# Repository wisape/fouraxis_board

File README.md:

# fouraxis_board-
A 4 axis board sch and pcb, which use the software KICAD

the board use the stm32
then sensor use mpu6050, and hmc5883l
and the wireless use nrf24l01

### pcb

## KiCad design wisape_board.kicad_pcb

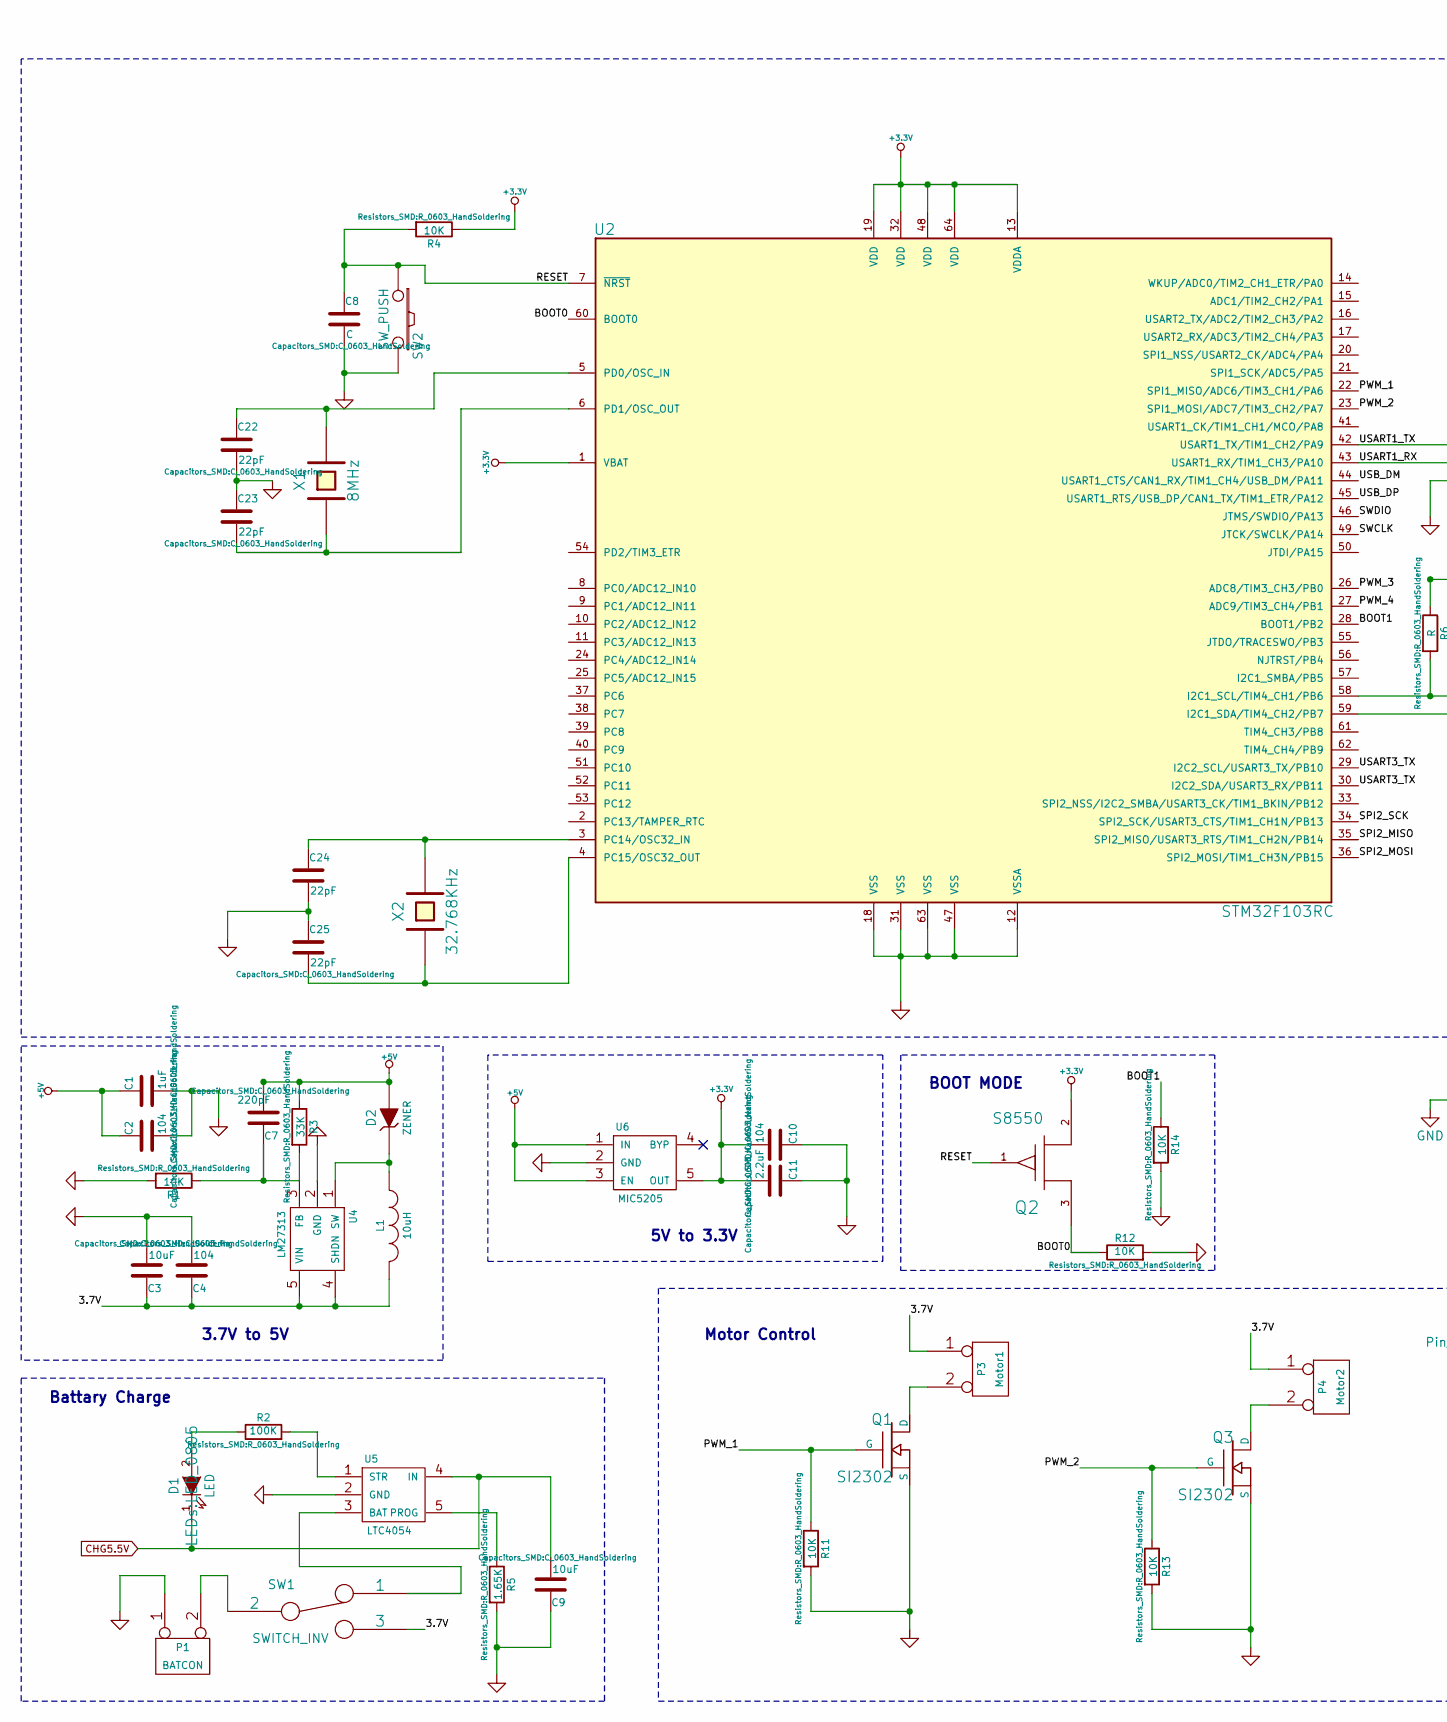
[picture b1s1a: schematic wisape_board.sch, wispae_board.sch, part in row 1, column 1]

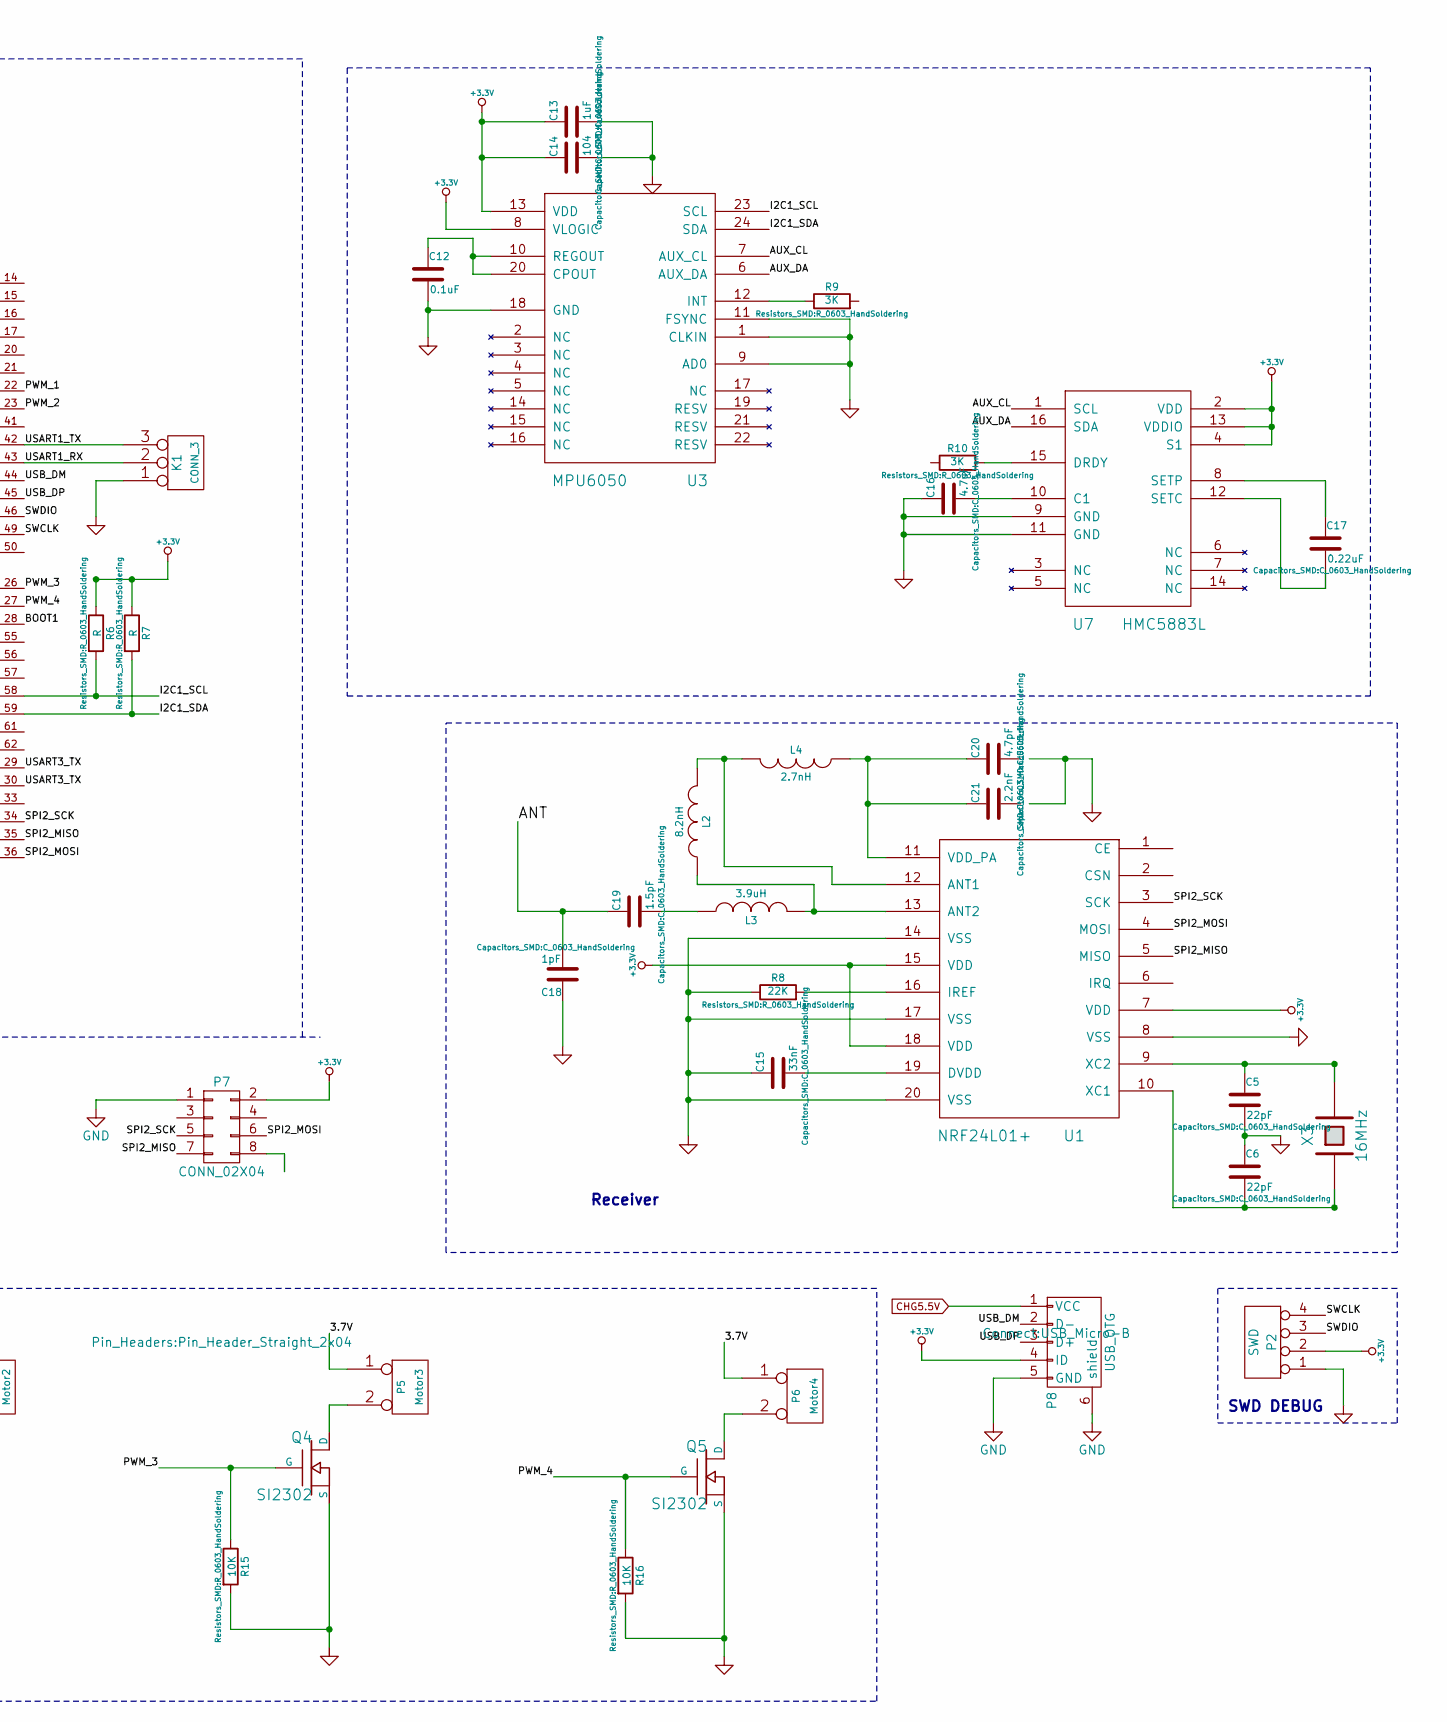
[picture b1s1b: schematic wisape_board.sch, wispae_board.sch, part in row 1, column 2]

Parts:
C1, C13: 1uF; C_0603_HandSoldering
C2, C4, C10, C14: 104; C_0603_HandSoldering
C3, C9: 10uF; C_0603_HandSoldering
C5, C6, C22, C23, C24, C25: 22pF; C_0603_HandSoldering
C7: 220pF; C_0603_HandSoldering
C8: C; C_0603_HandSoldering
C11: 2.2uF; C_0603_HandSoldering
C12: 0.1uF; C_0603_HandSoldering
C15: 33nF; C_0603_HandSoldering
C16: 4.7uF; C_0603_HandSoldering
C17: 0.22uF; C_0603_HandSoldering
C18: 1pF; C_0603_HandSoldering
C19: 1.5pF; C_0603_HandSoldering
C20: 4.7pF; C_0603_HandSoldering
C21: 2.2nF; C_0603_HandSoldering
D1: LED; LED_0805
D2: ZENER; SOD-123
K1: CONN_3; Pin_Header_Straight_1x03
L1: 10uH; Neosid_Inductor_SM0603CG
L2: 8.2nH; Neosid_Inductor_SM0603CG
L3: 3.9uH; Neosid_Inductor_SM0603CG
L4: 2.7nH; Neosid_Inductor_SM0603CG
P1: BATCON; Pin_Header_Straight_1x02
P2: SWD; Pin_Header_Straight_1x04
P3: Motor1; Pin_Header_Straight_1x02
P4: Motor2; Pin_Header_Straight_1x02
P5: Motor3; Pin_Header_Straight_1x02
P6: Motor4; Pin_Header_Straight_1x02
P7: CONN_02X04; Pin_Header_Straight_2x04
P8: USB_OTG; USB_Micro-B
Q1, Q3, Q4, Q5: SI2302; SOT-23
Q2: S8550; SOT-23
R1, R4, R11, R12, R13, R14, R15, R16: 10K; R_0603_HandSoldering
R2: 100K; R_0603_HandSoldering
R3: 33K; R_0603_HandSoldering
R5: 1.65K; R_0603_HandSoldering
R6, R7: R; R_0603_HandSoldering
R8: 22K; R_0603_HandSoldering
R9, R10: 3K; R_0603_HandSoldering
SW1: SWITCH_INV; SW_Micro_SPST
SW2: SW_PUSH; Switch_SMD_3_6_2.5
U1: NRF24L01+; QFN-20-1EP_4x4mm_Pitch0.5mm
U2: STM32F103RC; LQFP-64_10x10mm_Pitch0.5mm
U3: MPU6050; QFN-24-1EP_4x4mm_Pitch0.5mm
U4: LM27313; SOT-23-5
U5: LTC4054; SOT-23-5
U6: MIC5205; SOT-23-5
U7: HMC5883L; QFN-16-1EP_3x3mm_Pitch0.5mm
X1: 8MHz; Crystal_HC49-SD_SMD
X2: 32.768KHz; Crystal_Round_Vertical_3mm
X3: 16MHz; Crystal_HC49-SD_SMD

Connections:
+3.3V: C10.2, C11.2, C13.1, C14.1, P2.2, P7.2, P8.4 (ID), Q2.2 (S), R4.1, R6.1, R7.1, U1.7 (VDD), U1.15 (VDD), U1.18 (VDD), U2.1 (VBAT), U2.13 (VDDA), U2.19 (VDD), U2.32 (VDD), U2.48 (VDD), U2.64 (VDD), U3.8 (VLOGIC), U3.13 (VDD), U6.5 (OUT), U7.2 (VDD), U7.4 (S1), U7.13 (VDDIO)
+5V: C1.1, C2.1, C7.2, D2.2 (A), R3.1, U6.1 (IN), U6.3 (EN)
/3.7V: C3.1, C4.1, L1.2, P3.1, P4.1, P5.1, P6.1, SW1.3, U4.4 (SHDN), U4.5 (VIN)
/ANT: C18.2, C19.1
/AUX_CL: U3.7 (AUX_CL), U7.1 (SCL)
/AUX_DA: U3.6 (AUX_DA), U7.16 (SDA)
/BOOT0: Q2.3 (D), R12.1, U2.60 (BOOT0)
/BOOT1: R14.1, U2.28 (BOOT1/PB2)
/I2C1_SCL: R6.2, U2.58 (I2C1_SCL/TIM4_CH1/PB6), U3.23 (SCL)
/I2C1_SDA: R7.2, U2.59 (I2C1_SDA/TIM4_CH2/PB7), U3.24 (SDA)
/PWM_1: Q1.1 (G), R11.1, U2.22 (SPI1_MISO/ADC6/TIM3_CH1/PA6)
/PWM_2: Q3.1 (G), R13.1, U2.23 (SPI1_MOSI/ADC7/TIM3_CH2/PA7)
/PWM_3: Q4.1 (G), R15.1, U2.26 (ADC8/TIM3_CH3/PB0)
/PWM_4: Q5.1 (G), R16.1, U2.27 (ADC9/TIM3_CH4/PB1)
/RESET: C8.1, Q2.1 (G), R4.2, SW2.1, U2.7 (~NRST)
/SPI2_MISO: P7.7, U1.5 (MISO), U2.35 (SPI2_MISO/USART3_RTS/TIM1_CH2N/PB14)
/SPI2_MOSI: P7.6, U1.4 (MOSI), U2.36 (SPI2_MOSI/TIM1_CH3N/PB15)
/SPI2_SCK: P7.5, U1.3 (SCK), U2.34 (SPI2_SCK/USART3_CTS/TIM1_CH1N/PB13)
/SWCLK: P2.4, U2.49 (JTCK/SWCLK/PA14)
/SWDIO: P2.3, U2.46 (JTMS/SWDIO/PA13)
/USART1_RX: K1.2 (PM), U2.43 (USART1_RX/TIM1_CH3/PA10)
/USART1_TX: K1.3, U2.42 (USART1_TX/TIM1_CH2/PA9)
/USART3_TX: U2.29 (I2C2_SCL/USART3_TX/PB10), U2.30 (I2C2_SDA/USART3_RX/PB11)
/USB_DM: P8.2 (D-), U2.44 (USART1_CTS/CAN1_RX/TIM1_CH4/USB_DM/PA11)
/USB_DP: P8.3 (D+), U2.45 (USART1_RTS/USB_DP/CAN1_TX/TIM1_ETR/PA12)
CHG5.5V: C9.2, D1.1 (K), P8.1 (VCC), U5.4 (IN)
GND: C1.2, C2.2, C3.2, C4.2, C5.2, C6.1, C8.2, C9.1, C10.1, C11.1, C12.2, C13.2, C14.2, C15.1, C16.1, C18.1, C22.2, C23.1, C24.2, C25.1, K1.1, P1.1, P2.1, P7.1, P8.5 (GND), P8.6 (shield), Q1.2 (S), Q3.2 (S), Q4.2 (S), Q5.2 (S), R1.2, R5.2, R8.1, R11.2, R12.2, R13.2, R14.2, R15.2, R16.2, SW2.2, U1.8 (VSS), U1.14 (VSS), U1.17 (VSS), U1.20 (VSS), U2.12 (VSSA), U2.18 (VSS), U2.31 (VSS), U2.47 (VSS), U2.63 (VSS), U3.1 (CLKIN), U3.9 (AD0), U3.11 (FSYNC), U3.18 (GND), U4.2 (GND), U5.2 (GND), U6.2 (GND), U7.9 (GND), U7.11 (GND)
unnamed: C5.1, U1.9 (XC2), X3.2
unnamed: C6.2, U1.10 (XC1), X3.1
unnamed: C7.1, R1.1, R3.2, U4.3 (FB)
unnamed: C12.1, U3.10 (REGOUT), U3.20 (CPOUT)
unnamed: C15.2, U1.19 (DVDD)
unnamed: C16.2, U7.10 (C1)
unnamed: C17.1, U7.8 (SETP)
unnamed: C17.2, U7.12 (SETC)
unnamed: C19.2, L3.1
unnamed: C20.1, C21.1, L4.1, U1.11 (VDD_PA)
unnamed: C22.1, U2.5 (PD0/OSC_IN), X1.2
unnamed: C23.2, U2.6 (PD1/OSC_OUT), X1.1
unnamed: C24.1, U2.3 (PC14/OSC32_IN), X2.2
unnamed: C25.2, U2.4 (PC15/OSC32_OUT), X2.1
unnamed: D1.2 (A), R2.1
unnamed: D2.1 (K), L1.1, U4.1 (SW)
unnamed: L2.1, L3.2, U1.13 (ANT2)
unnamed: L2.2, L4.2, U1.12 (ANT1)
unnamed: P1.2 (PM), SW1.2
unnamed: P3.2 (PM), Q1.3 (D)
unnamed: P4.2 (PM), Q3.3 (D)
unnamed: P5.2 (PM), Q4.3 (D)
unnamed: P6.2 (PM), Q5.3 (D)
unnamed: R2.2, U5.1 (STR)
unnamed: R5.1, U5.5 (PROG)
unnamed: R8.2, U1.16 (IREF)
unnamed: R9.1, U3.12 (INT)
unnamed: R10.2, U7.15 (DRDY)
unnamed: SW1.1, U5.3 (BAT)

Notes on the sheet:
3.7V to 5V
5V to 3.3V
Battary Charge
Receiver
SWD DEBUG
BOOT MODE
Motor Control

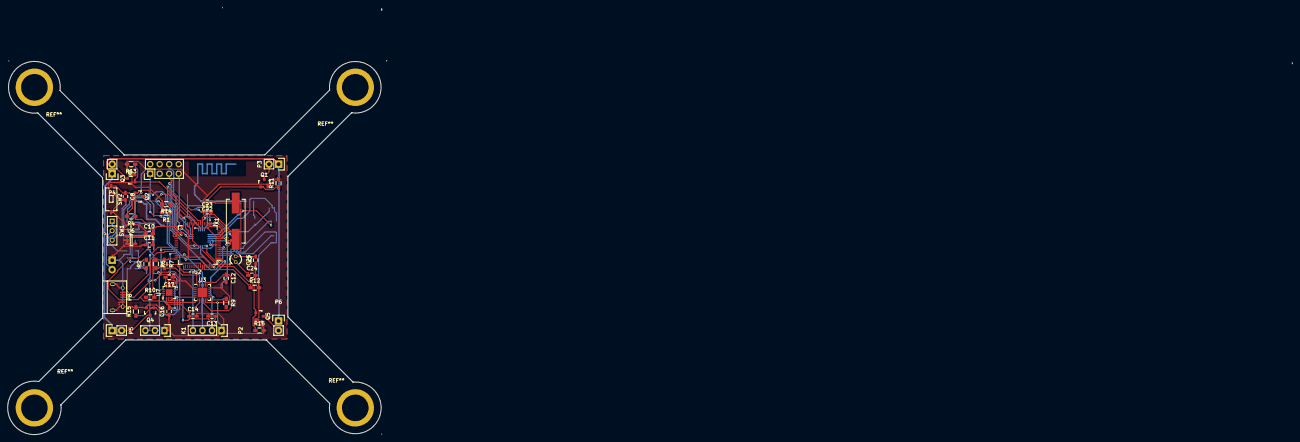
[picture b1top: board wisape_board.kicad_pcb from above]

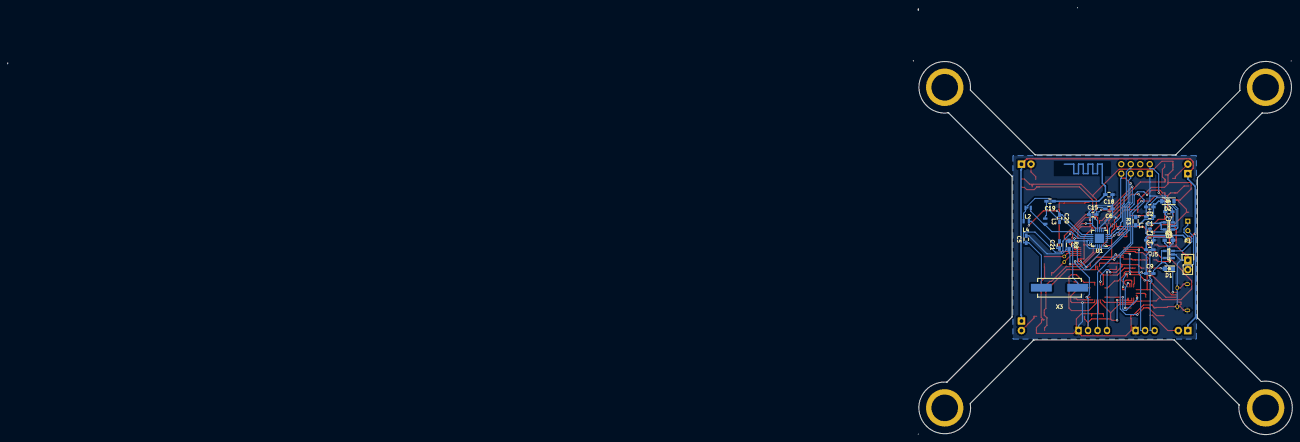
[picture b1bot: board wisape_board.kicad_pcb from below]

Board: 2 copper layers, 343.2 x 114.0 mm, 73 parts (27 on the bottom side), 56 nets.

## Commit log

2017-08-19 Init the source code
2017-08-19 add the pcb board picture
2017-08-19 add the pcb picture in readme
